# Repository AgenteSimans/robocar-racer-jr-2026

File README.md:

# 🏎️ Robocar Jr — Placa de Controle & Gerenciamento
### Robocar Race 2025 · hardware em KiCad 10

> Corpo de prova eletrônico de um carro autônomo de competição, projetado no **KiCad** para
> concentrar, em uma única placa, o cérebro (**ESP32‑DEVKITC**), o copiloto embarcado
> (**Raspberry Pi**), os sensores de navegação (**GY‑87**), a medição de energia (**ADS1115**)
> e toda a interface de potência dos atuadores (servo de direção + ESC/motor BLDC).

---

## ✨ O que a placa faz

| Bloco | Papel no veículo |
|-------|------------------|
| 🧠 **ESP32‑DEVKITC** | Controlador em tempo real (sensores, PWM, decisão), montado em soquete. |
| 🍓 **Raspberry Pi** | Co‑processador de visão/navegação, ligado ao ESP32 por **UART** e alimentado via **USB‑C** na placa. |
| 🧭 **GY‑87 (IMU)** | Orientação e movimento — MPU6050 + HMC5883L + BMP280, em barramento I²C. |
| 📊 **ADS1115** | ADC externo de **16 bits** (I²C) com **4 canais** para medição precisa de bateria e dos rails de potência. |
| ⚡ **Gestão de energia** | Conversor **Buck** (+5 V) e conversor **Step‑up** (+8 V / +12 V) a partir da bateria, com chaves de comutação. |
| 🎯 **Atuadores** | Saída dedicada para **servo** (direção, 5 V) e para **ESC/motor BLDC** (tração, 12 V de potência + sinal 5 V). |
| 💡 **Feedback visual** | LEDs de estado (**Estado_1/2/3**) e LEDs de presença de tensão (**+BV**, **+12 V**). |
| 📡 **Enlace serial** | UART `TX/RX_RASPBERRY` para telemetria e troca de comandos ESP32 ↔ Raspberry. |
| 🎮 **Modo manual (opcional)** | Previsão de entradas de receptor RC (`Radio`, `Servo Rec`, `Motor Rec`). |

---

## ⚡ Arquitetura de potência

A bateria (`+BV`) é a fonte primária e é distribuída/comutada por **chaves DPST (SW1/SW2)**.
Dois estágios de conversão DC‑DC geram os rails usados pelo sistema:

| Rail | Gerado por | Alimenta |
|------|-----------|----------|
| **+5 V** (`Buck_out`) | Conversor **Buck** (`Buck_in` → `Buck_out`) | Lógica de sinal, **servo motor**, barramento do enlace |
| **+3,3 V** | Regulação a partir de +5 V | **ESP32**, **GY‑87**, **ADS1115** |
| **+8 V** | Bateria 2S | Alimentação do Motor |
| **+12 V** | Bateria 3S | Alimentação do Esp32 e Raspberry  |
| **USB‑C 5 V** | Conector `Raspbery_usbc` | **Raspberry Pi** |

> O **servo** recebe potência e sinal em 5 V (conector `J3`); o **motor/ESC** recebe a
> potência de 12 V pelo conector `Motor in` (`J11`) e o sinal PWM de 5 V pelo conector `J4` —
> separando claramente o caminho de potência do caminho de controle.

---

## 📊 Monitoramento de bateria e de rails (ADS1115)

Quatro entradas analógicas, todas condicionadas por **divisores resistivos + filtro RC**,
lidas com resolução de 16 bits (muito mais estáveis que o ADC interno do ESP32):

| Canal | Origem medida | Sentido |
|:-----:|---------------|---------|
| **A0** | Divisor de Tensão da Bateria 3S | Tensão da Bateria 3S |
| **A1** | Divisor de Tensão da Bateria 2S | Tensão da Bateria 2S |

Endereço I²C do ADS1115 com `ADDR` amarrado ao GND (**0x48**); `ALERT` usado conforme estratégia de firmware (polling ou interrupção).

---

## 🔗 Comunicação & interfaces

- **I²C (compartilhado):** `SDA` e `SCL` ligam **GY‑87** e **ADS1115** ao ESP32.
- **UART ↔ Raspberry:** pares `TX_RASPBERRY` / `RX_RASPBERRY` formam o enlace serial
  ESP32 ⇄ Raspberry (telemetria, comandos, handshake de missão).
- **Sinais de controle:** `Sinal_Servo` (direção) e `Sinal_Motor` (tração via ESC).
- **Feedback luminoso:** `Estado_1`, `Estado_2`, `Estado_3` (LEDs 3 mm, R = 220 Ω) indicam a
  fase/estado da máquina; LEDs adicionais sinalizam presença de **+BV** (R = 330 Ω) e **+12 V** (R = 1 kΩ).
- **Chaves:** `SW1`/`SW2` (DPST) para comutação/corte dos ramos de bateria e enlace.

---

## 🧱 Conectores de campo

| Ref. | Função | Sinais |
|------|--------|--------|
| **J7** | Módulo **GY‑87** | +3,3 V · SCL · SDA · GND |
| **J10** | Entrada do **Buck** | `Buck_in` · GND |
| **J11** | Potência do **motor** | +12 V (`Motor in`) · GND |
| **J3** | **Servo motor** | +5 V (`Buck_out`) · `Sinal_Servo` · GND |
| **J4** | Sinal do **ESC/motor** | +5 V · `Sinal_Motor` · GND |
| **J14** | **USB‑C do Raspberry** | +5 V · GND |
| **J15** | Saída do **Step‑up** | +12 V · GND |
| **J2 / J5** | Soquete / breakout **ESP32‑DEVKITC** | barramento completo do módulo |
| **SW1 / SW2** | Chaves DPST | comutação de bateria/enlace |

> A atribuição física de cada GPIO do ESP32 segue o soquete `J2`/`J5`; a referência canônica
> é o esquemático hierárquico incluído no projeto.

---

## 🖼️ Galeria

### Esquemático (hierárquico)
Blocos de baterias, entradas de motor/conversor Buck, barramento do Raspberry, conexões do
GY‑87, enlace serial, ADS1115, divisores de tensão e LEDs de feedback.

### Layout da PCB
Posicionamento dos conectores de bateria e de potência, soquete do ESP32, trilhas de 12 V /
5 V dimensionadas para corrente e separação cuidadosa entre potência e sinal.

---

## 📄 Licença & crédito

Hardware aberto sob licença **MIT** — use, estude e adapte como base para o seu Robocar Jr. 🏁

<sub>Projeto de competição · **Robocar Race 2025** · desenvolvido por **Pablo Nunes de Oliveira** · KiCad E.D.A. 10</sub>

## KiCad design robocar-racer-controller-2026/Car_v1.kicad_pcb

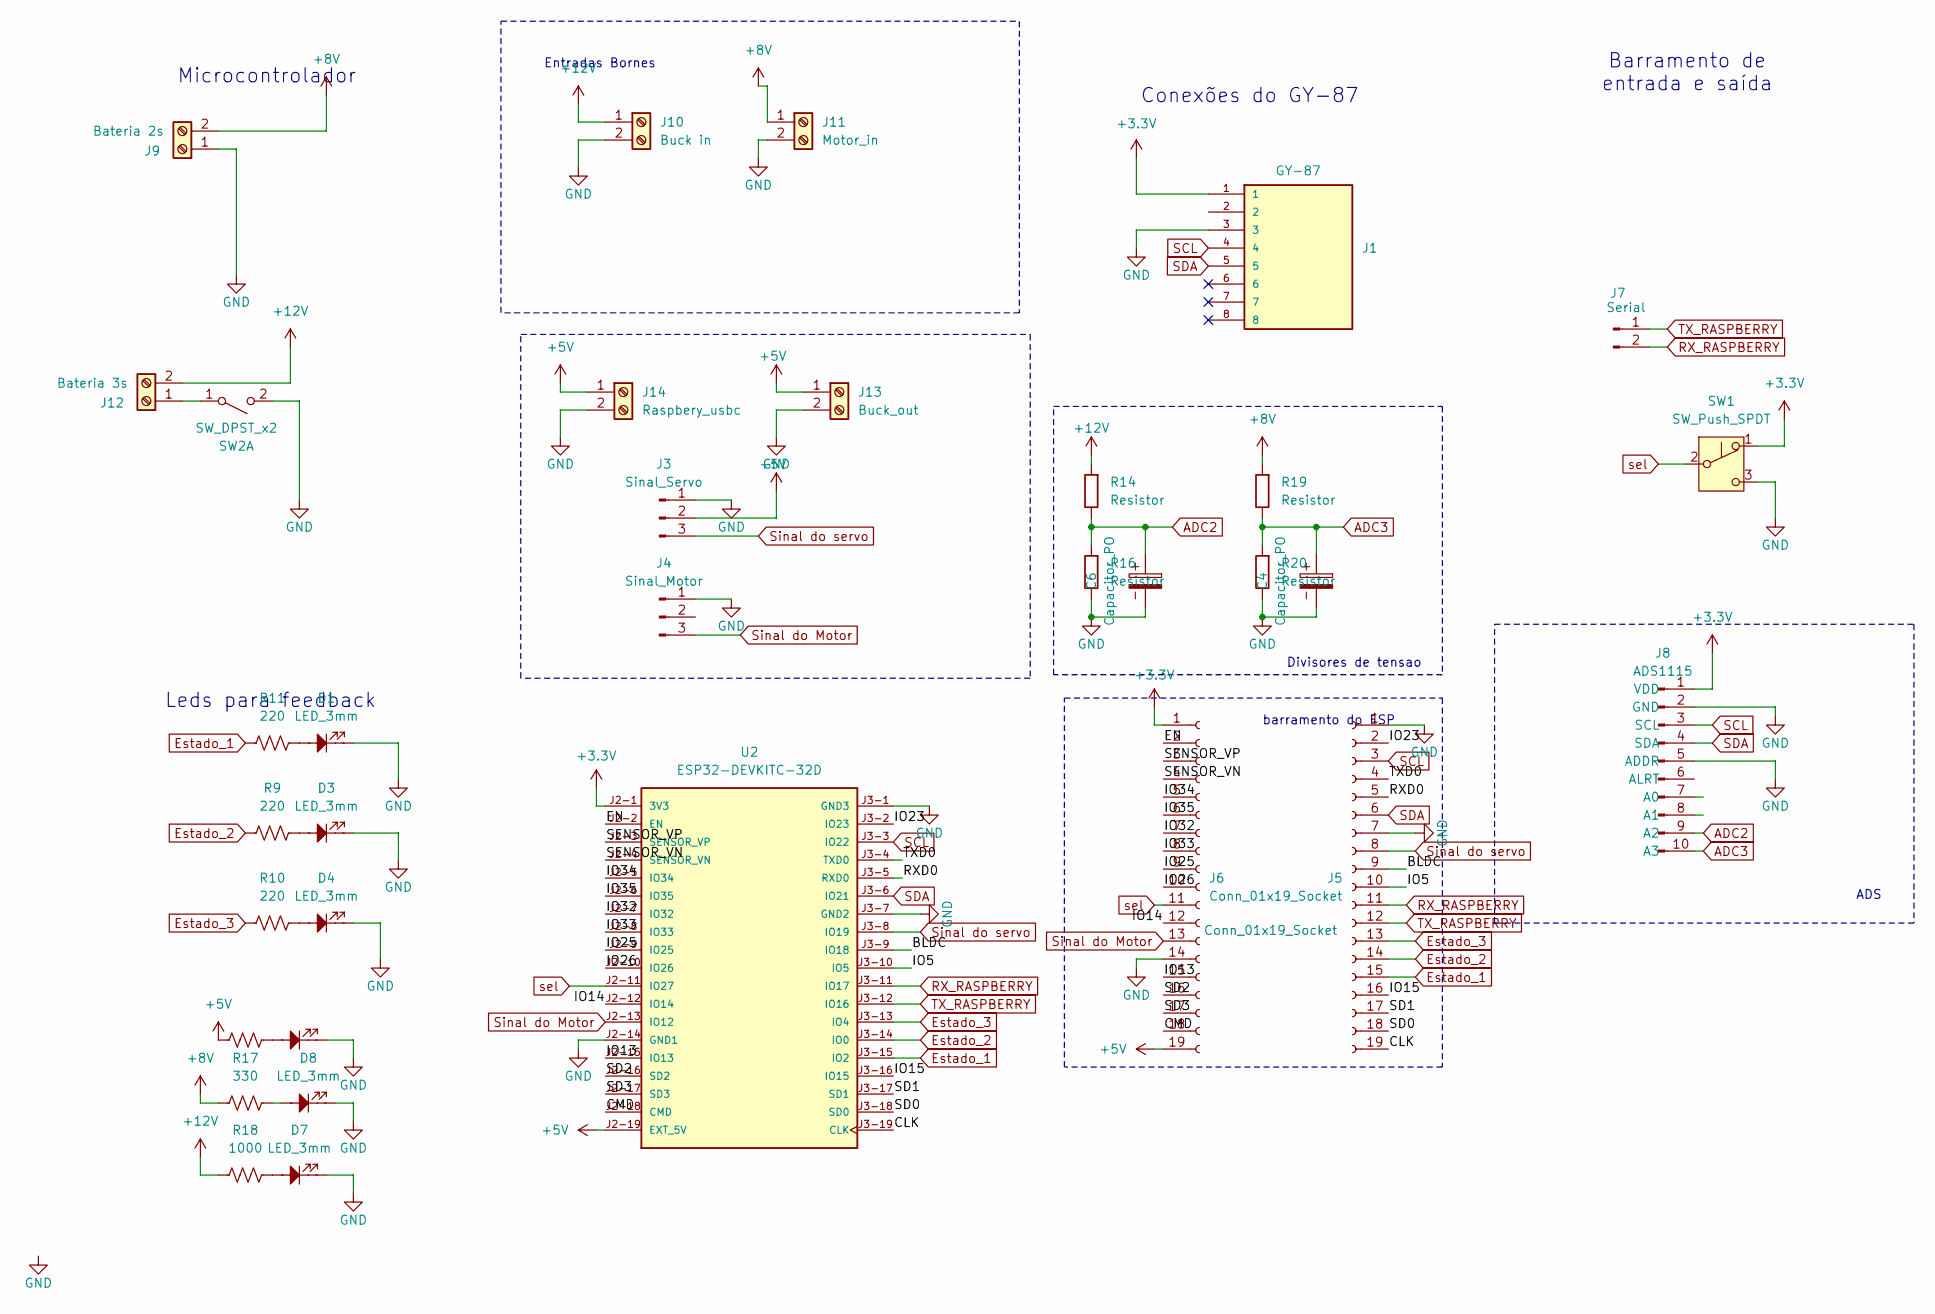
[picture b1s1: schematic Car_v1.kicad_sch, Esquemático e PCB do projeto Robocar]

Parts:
C4, C6: Capacitor_PO; CP_Radial_D5.0mm_P2.50mm
D1, D3, D4, D5, D7, D8: LED_3mm; LED_D3.0mm
J1: GY-87; Pins_1x08_2.54mm_TH; PARTREV R
J3: Sinal_Servo; PinHeader_1x03_P2.54mm_Horizontal
J4: Sinal_Motor; PinHeader_1x03_P2.54mm_Horizontal
J5, J6: Conn_01x19_Socket; PinHeader_1x19_P2.54mm_Vertical
J7: Serial; PinHeader_1x02_P2.54mm_Horizontal
J8: ADS1115; PinSocket_1x10_P2.54mm_Vertical
J9: Bateria 2s; TerminalBlock_Phoenix_MKDS-1,5-2-5.08_1x02_P5.08mm_Horizont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
J10: Buck in; TerminalBlock_Phoenix_MKDS-1,5-2-5.08_1x02_P5.08mm_Horizont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
J11: Motor_in; TerminalBlock_Phoenix_MKDS-1,5-2-5.08_1x02_P5.08mm_Horizont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
J12: Bateria 3s; TerminalBlock_Phoenix_MKDS-1,5-2-5.08_1x02_P5.08mm_Horizont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
J13: Buck_out; TerminalBlock_Phoenix_MKDS-1,5-2-5.08_1x02_P5.08mm_Horizont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
J14: Raspbery_usbc; TerminalBlock_Phoenix_MKDS-1,5-2-5.08_1x02_P5.08mm_Horizont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
R9, R10, R11, R12: 220; R_Axial_DIN0309_L9.0mm_D3.2mm_P12.70mm_Horizontal
R14, R16, R19, R20: Resistor; R_Axial_DIN0207_L6.3mm_D2.5mm_P10.16mm_Horizontal
R17: 330; R_Axial_DIN0309_L9.0mm_D3.2mm_P12.70mm_Horizontal
R18: 1000; R_Axial_DIN0309_L9.0mm_D3.2mm_P12.70mm_Horizontal
SW1: SW_Push_SPDT; SW_Slide-03_Wuerth-WS-SLTV_10x2.5x6.4_P2.54mm
SW2: SW_DPST_x2; KCD1
U2: ESP32-DEVKITC-32D; MODULE_ESP32-DEVKITC-32D; PARTREV V4

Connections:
+3.3V: J1.1, J6.1, J8.1 (VDD), SW1.1 (A), U2.J2-1 (3V3)
+5V: J3.2, J6.19, J13.1, J14.1, R12.1, U2.J2-19 (EXT_5V)
+8V: J9.2, J11.1, R17.1, R19.1
+12V: J10.1, J12.2, R14.1, R18.1
/BLDC: J5.9, U2.J3-9 (IO18)
/CLK: J5.19, U2.J3-19 (CLK)
/CMD: J6.18, U2.J2-18 (CMD)
/EN: J6.2, U2.J2-2 (EN)
/IO5: J5.10, U2.J3-10 (IO5)
/IO13: J6.15, U2.J2-15 (IO13)
/IO14: J6.12, U2.J2-12 (IO14)
/IO15: J5.16, U2.J3-16 (IO15)
/IO23: J5.2, U2.J3-2 (IO23)
/IO25: J6.9, U2.J2-9 (IO25)
/IO32: J6.7, U2.J2-7 (IO32)
/IO33: J6.8, U2.J2-8 (IO33)
/IO34: J6.5, U2.J2-5 (IO34)
/IO35: J6.6, U2.J2-6 (IO35)
/RXD0: J5.5, U2.J3-5 (RXD0)
/SD0: J5.18, U2.J3-18 (SD0)
/SD1: J5.17, U2.J3-17 (SD1)
/SD2: J6.16, U2.J2-16 (SD2)
/SD3: J6.17, U2.J2-17 (SD3)
/SENSOR_VN: J6.4, U2.J2-4 (SENSOR_VN)
/SENSOR_VP: J6.3, U2.J2-3 (SENSOR_VP)
/TXD0: J5.4, U2.J3-4 (TXD0)
ADC2: C6.1, J8.9 (A2), R14.2, R16.1
ADC3: C4.1, J8.10 (A3), R19.2, R20.1
Estado_1: J5.15, R11.1, U2.J3-15 (IO2)
Estado_2: J5.14, R9.1, U2.J3-14 (IO0)
Estado_3: J5.13, R10.1, U2.J3-13 (IO4)
GND: C4.2, C6.2, D1.1, D3.1, D4.1, D5.1, D7.1, D8.1, J1.3, J3.1, J4.1, J5.1, J5.7, J6.14, J8.2 (GND), J8.5 (ADDR), J9.1, J10.2, J11.2, J13.2, J14.2, R16.2, R20.2, SW1.3 (C), SW2.2 (B), U2.J2-14 (GND1), U2.J3-1 (GND3), U2.J3-7 (GND2)
INTA: J1.7, J6.10, U2.J2-10 (IO26)
unnamed: D1.2, R11.2
unnamed: D3.2, R9.2
unnamed: D4.2, R10.2
unnamed: D5.2, R12.2
unnamed: D7.2, R18.2
unnamed: D8.2, R17.2
unnamed: J12.1, SW2.1 (A)
RX_RASPBERRY: J5.11, J7.2, U2.J3-11 (IO17)
SCL: J1.4, J5.3, J8.3 (SCL), U2.J3-3 (IO22)
SDA: J1.5, J5.6, J8.4 (SDA), U2.J3-6 (IO21)
Sinal do Motor: J4.3, J6.13, U2.J2-13 (IO12)
Sinal do servo: J3.3, J5.8, U2.J3-8 (IO19)
TX_RASPBERRY: J5.12, J7.1, U2.J3-12 (IO16)
sel: J6.11, SW1.2 (B), U2.J2-11 (IO27)

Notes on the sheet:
Conexões do GY-87
Barramento de entrada e saída
barramento do ESP
Divisores de tensao
Entradas Bornes
Leds para feedback
Microcontrolador
ADS

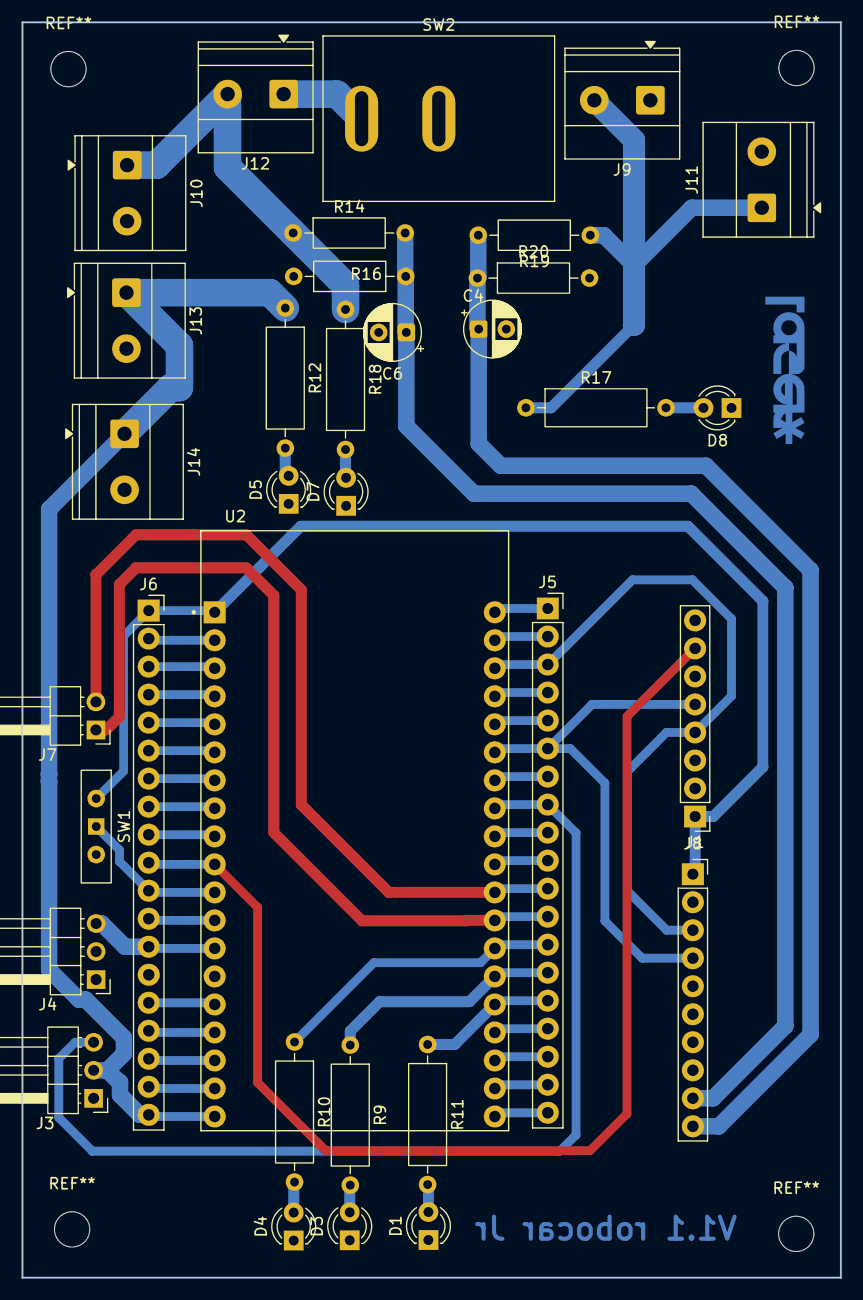
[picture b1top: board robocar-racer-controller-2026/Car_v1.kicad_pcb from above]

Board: 2 copper layers, 74.2 x 113.8 mm, 34 parts (0 on the bottom side), 47 nets.

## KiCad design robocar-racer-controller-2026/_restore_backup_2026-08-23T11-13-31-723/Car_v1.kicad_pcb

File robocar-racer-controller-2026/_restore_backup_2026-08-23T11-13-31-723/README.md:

# robocar-racer-controller-2025

## Visão Geral
Este repositório contém o projeto de hardware da **placa controladora** desenvolvida pela **Equipe Laser** para a competição **Robocar Racer 2025**. A placa recebe e interpreta dados da **Raspberry Pi** para controlar o motor brushless (ESC) e o servo motor, implementando isolamento galvânico e redundância via rádio controle.

---

## Visualização do Projeto

### Modelo 3D

### Documentação Técnica (PDF)
Para detalhes de roteamento e conexões, acesse os arquivos abaixo:
* [📄 Esquemático Completo](Assets/Esquemático.pdf)
* [📄 Layout da PCB](Assets/PCB_layout.pdf)

---

## Especificações Técnicas
* **Microcontrolador:** ESP32 (NodeMCU/DevKit V1)
* **Software de EDA:** KiCad 8.0.6
* **Dimensões da PCB:** 91.00 mm x 67.75 mm
* **Isolamento:** Optoacopladores **PC817** (Separação entre lógica/USB e potência/Bateria).

## Operação e Segurança
O sistema gerencia a tração e direção do veículo em três estados:
1. **Modo Autônomo:** Controle via Raspberry Pi (Serial/USB).
2. **Modo Manual (Radio):** Redundância via rádio controle externo (Fail-safe).
3. **Modo Neutro:** Veículo parado por segurança.

## Interfaces de Hardware
* **Barramento GY-87:** Conexão I2C para IMU (Telemetria e estabilização).
* **Feedback Visual:** 4 LEDs (Power, Estado 1, Estado 2, Estado 3).
* **Isolamento de Terra:** Separação física entre `GND_CAR` e `Earth` (GND lógico).

## Estrutura do Repositório
* **`/Gerber`**: Arquivos finais de fabricação e furação.
* **`/Assets`**: Fotos, modelos 3D e documentação técnica em PDF.
* **`/Meus footprints.pretty`**: Biblioteca de footprints personalizados.
* **`Car_v1.kicad_...`**: Arquivos fonte do projeto para edição no KiCad.

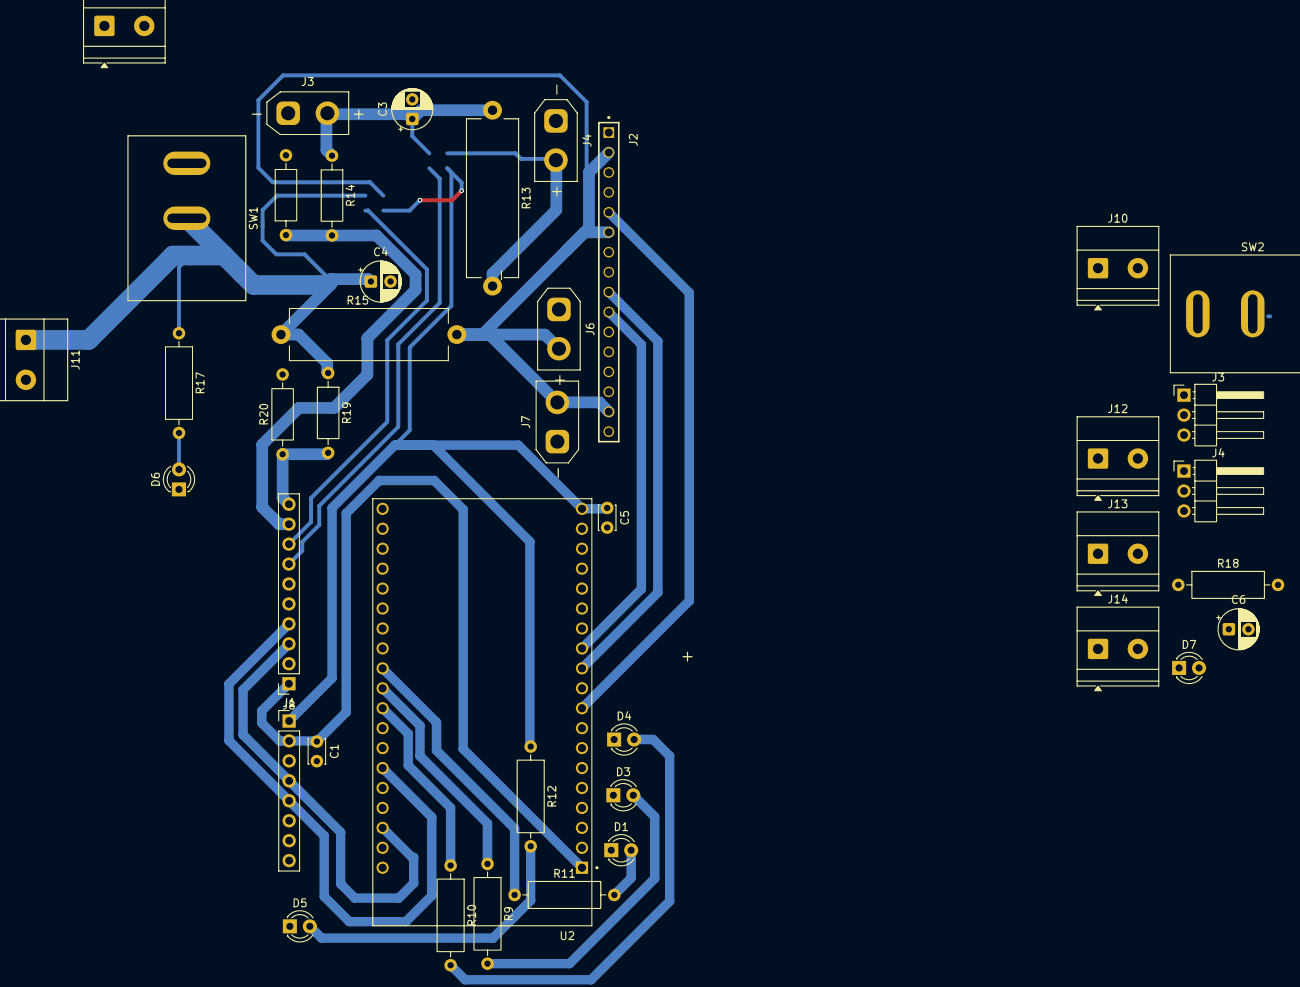
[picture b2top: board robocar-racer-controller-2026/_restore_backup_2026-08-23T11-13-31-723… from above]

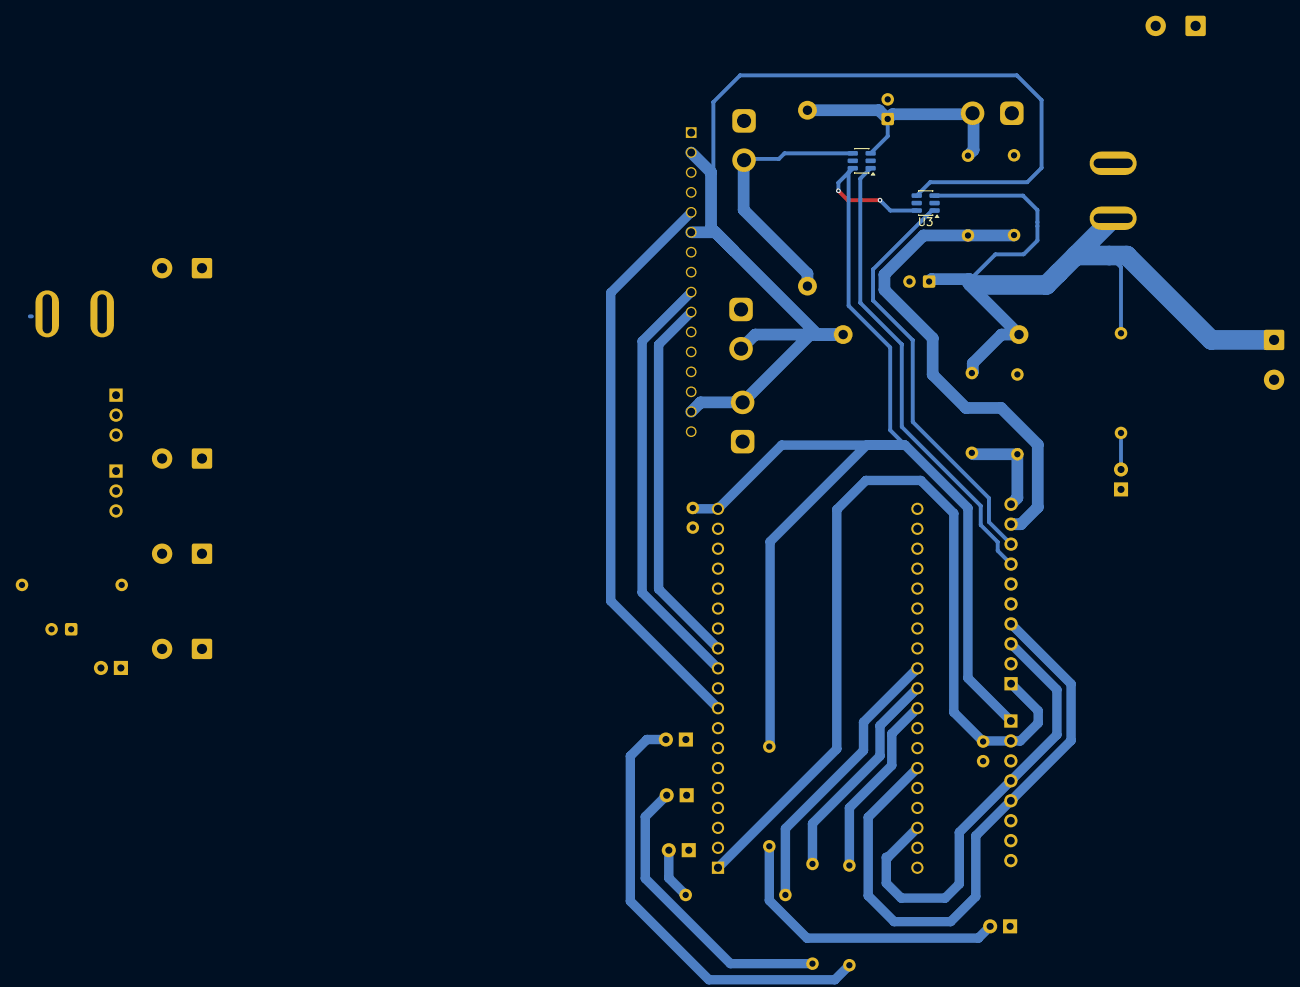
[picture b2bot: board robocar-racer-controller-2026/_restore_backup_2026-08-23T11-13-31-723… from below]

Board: 2 copper layers, 43 parts (2 on the bottom side), 30 nets.

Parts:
C1: 0.1uF; C_Disc_D3.0mm_W2.0mm_P2.50mm
C3, C4, C6: Capacitor_PO; CP_Radial_D5.0mm_P2.50mm
C5: 100mF; C_Disc_D3.0mm_W2.0mm_P2.50mm
D1, D3, D4, D5, D6, D7: LED_3mm; LED_D3.0mm
J1: GY-87; Pins_1x08_2.54mm_TH
J2: Barramento 16 pinos; SAMTEC_TSW-116-22-T-S
J3, J4#2: Conn_01x03_Pin; PinHeader_1x03_P2.54mm_Horizontal
J3#2: Bateria 3s; AMASS_XT30UPB-F_1x02_P5.0mm_Vertical
J4: Buck 5v; AMASS_XT30UPB-F_1x02_P5.0mm_Vertical
J6: Stepup; AMASS_XT30UPB-F_1x02_P5.0mm_Vertical
J7: ESC; AMASS_XT30UPB-F_1x02_P5.0mm_Vertical
J8: ADS1115; PinSocket_1x10_P2.54mm_Vertical
J9: Bateria 2s; TerminalBlock_Phoenix_MKDS-1,5-2-5.08_1x02_P5.08mm_Horizont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
J10: Buck in; TerminalBlock_Phoenix_MKDS-1,5-2-5.08_1x02_P5.08mm_Horizont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
J11: Motor_in; TerminalBlock_Phoenix_MKDS-1,5-2-5.08_1x02_P5.08mm_Horizont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
J12: Bateria 3s; TerminalBlock_Phoenix_MKDS-1,5-2-5.08_1x02_P5.08mm_Horizont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
J13: Buck_out; TerminalBlock_Phoenix_MKDS-1,5-2-5.08_1x02_P5.08mm_Horizont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
J14: Raspbery_usbc; TerminalBlock_Phoenix_MKDS-1,5-2-5.08_1x02_P5.08mm_Horizont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
R9, R10, R11, R12: 220; R_Axial_DIN0309_L9.0mm_D3.2mm_P12.70mm_Horizontal
R13, R15: Shunt; R_Axial_Power_L20.0mm_W6.4mm_P22.40mm
R14, R16, R19, R20: Resistor; R_Axial_DIN0207_L6.3mm_D2.5mm_P10.16mm_Horizontal
R17: 330; R_Axial_DIN0309_L9.0mm_D3.2mm_P12.70mm_Horizontal
R18: 1000; R_Axial_DIN0309_L9.0mm_D3.2mm_P12.70mm_Horizontal
SW1, SW2: SW_DPST_x2; KCD1
U1, U3: INA181; SOT-23-6
U2: ESP32-DEVKITC-32D; MODULE_ESP32-DEVKITC-32D

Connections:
5V: C5.1, R12.1, U1.6 (V+), U2.J2-19 (EXT_5V), U3.6 (V+)
12V: C3.1, J3#2.2, R13.1, U1.3 (+)
+3.3V: C1.1, J1.1, J8.1 (VDD), U2.J2-1 (3V3)
+5V: J3.2, J4#2.2, J13.1, J14.1
+8V: C4.1, J11.1, R15.1, R17.1, R19.1, SW1.2 (B), U3.3 (+)
+12V: C6.1, J10.1, R14.1, R18.1, SW2.2 (B)
ADC0: J8.7 (A0), U1.1
ADC1: J8.8 (A1), U3.1
ADC2: J8.9 (A2), R14.2, R16.1
ADC3: J8.10 (A3), R19.2, R20.1
Estado_1: R11.1, U2.J3-11 (IO17)
Estado_2: R9.1, U2.J3-10 (IO5)
Estado_3: R10.1, U2.J3-9 (IO18)
GND: C1.2, C3.2, C4.2, C5.2, C6.2, D1.1, D3.1, D4.1, D5.1, D6.1, D7.1, J1.3, J2.03, J2.07, J2.16, J3.1, J3#2.1, J4.1, J4#2.1, J6.1, J7.1, J8.2 (GND), J8.5 (ADDR), J9.1, J10.2, J11.2, J12.1, J13.2, J14.2, R16.2, R20.2, U1.2 (GND), U1.5 (REF), U2.J2-14 (GND1), U2.J3-1 (GND3), U2.J3-7 (GND2), U3.2 (GND), U3.5 (REF)
Motor Rec: J2.09, U2.J2-11 (IO27)
unnamed: D1.2, R11.2
unnamed: D3.2, R9.2
unnamed: D4.2, R10.2
unnamed: D5.2, R12.2
unnamed: D6.2, R17.2
unnamed: D7.2, R18.2
unnamed: J4.2, R13.2, U1.4 (-)
unnamed: J9.2, SW1.1 (A)
unnamed: J12.2, SW2.1 (A)
SCL: J1.4, J8.3 (SCL), U2.J3-3 (IO22)
SDA: J1.5, J8.4 (SDA), U2.J3-6 (IO21)
Servo Rec: J2.10, U2.J2-12 (IO14)
Sinal do Motor: J4#2.3, U2.J2-13 (IO12)
Sinal do servo: J2.05, J3.3, U2.J2-9 (IO25)
VCC_CAR: J2.02, J2.06, J2.15, J6.2, J7.2, R15.2, U3.4 (-)
